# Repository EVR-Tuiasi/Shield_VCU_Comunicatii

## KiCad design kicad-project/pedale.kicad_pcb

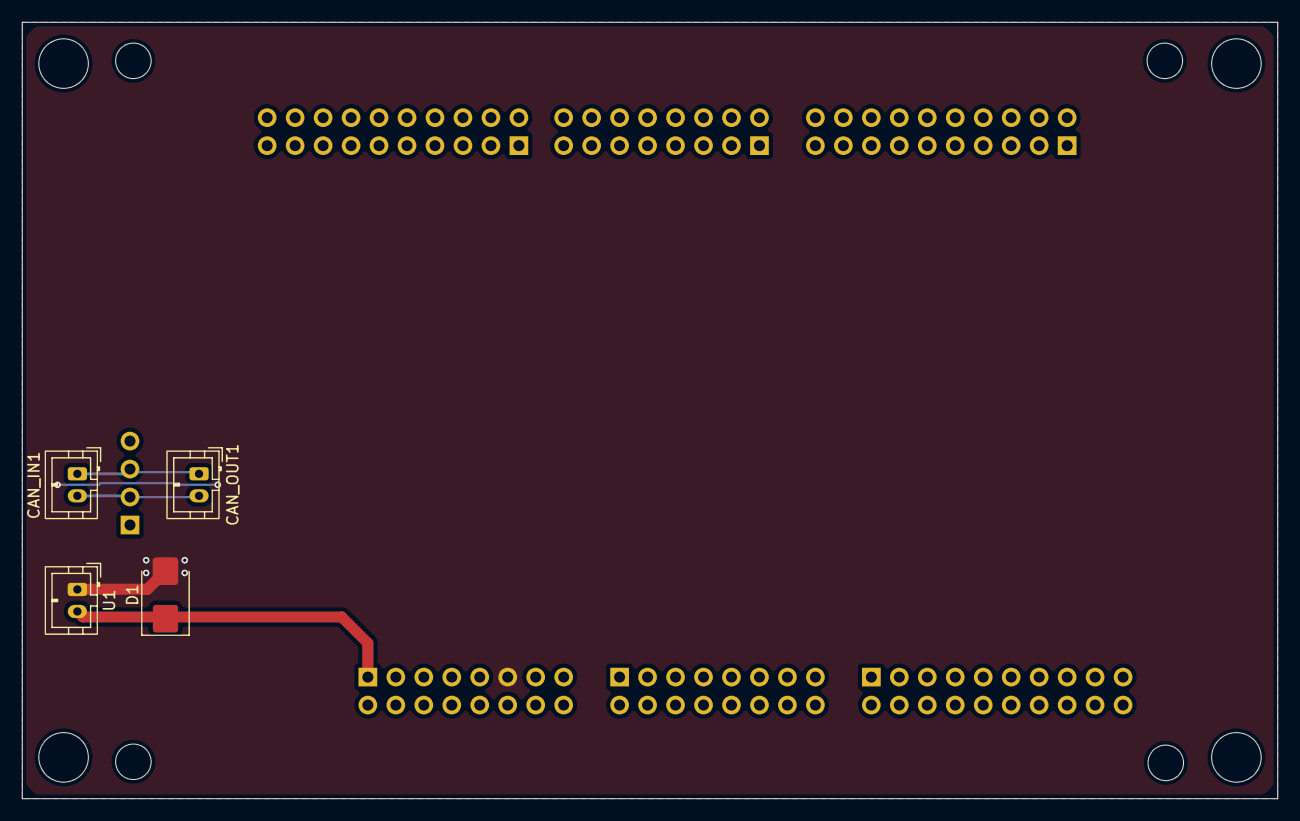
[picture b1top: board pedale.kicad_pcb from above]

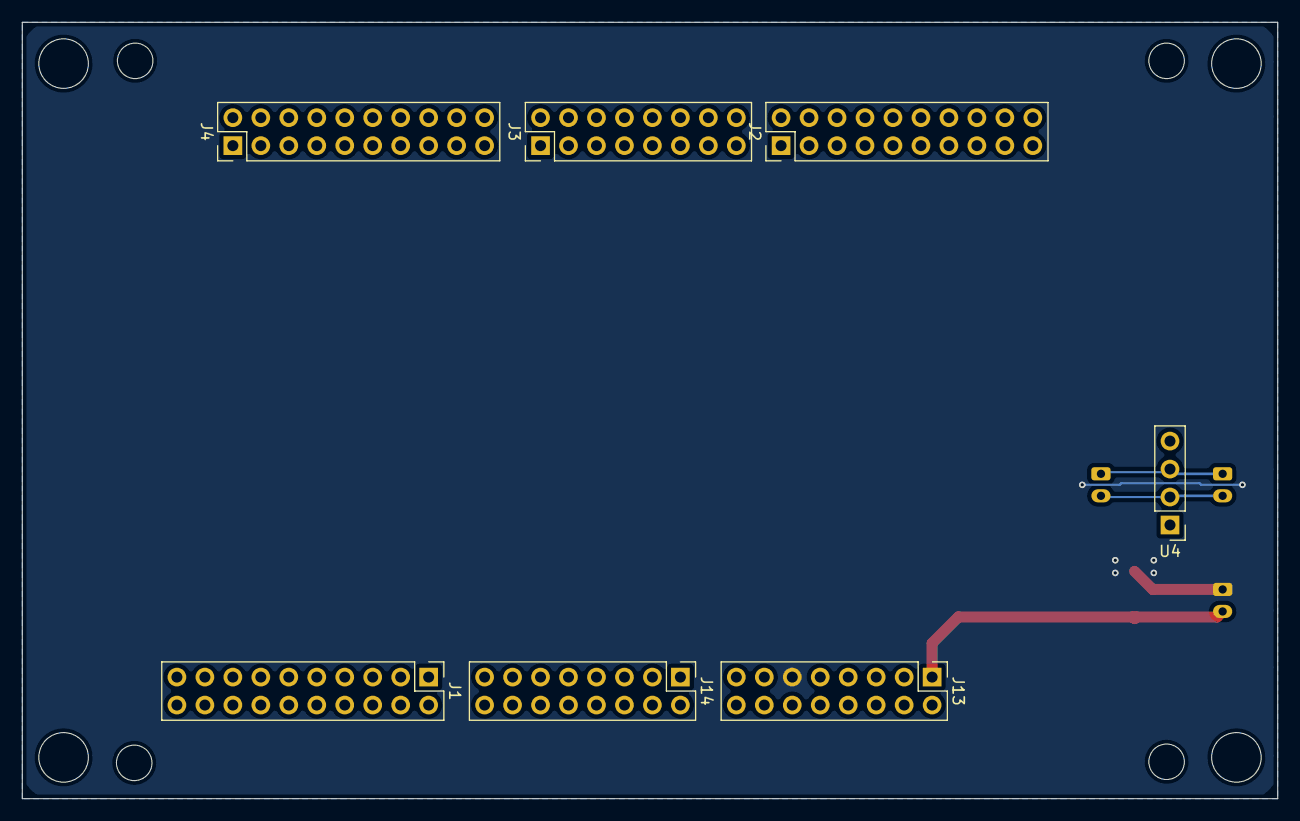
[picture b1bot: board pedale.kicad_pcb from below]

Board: 2 copper layers, 114.0 x 70.5 mm, 11 parts (7 on the bottom side), 4 nets.

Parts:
CAN_IN1: JST_PH_B2B-PH-K_1x02_P2.00mm_Vertical
CAN_OUT1: JST_PH_B2B-PH-K_1x02_P2.00mm_Vertical
D1: SS32; D_SMB
J1, J2, J4: PinHeader_2x10_P2.54mm_Vertical
J3, J13, J14: PinHeader_2x08_P2.54mm_Vertical
U1: JST_PH_B2B-PH-K_1x02_P2.00mm_Vertical
U4: PinHeader_1x04_P2.54mm_Vertical

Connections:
12V: D1.1 (K), J13.1 (VBAT), U1.2 (12V)
/CAN_N: CAN_IN1.2 (CANL), CAN_OUT1.2 (CANL), U4.2 (CANL)
/CAN_P: CAN_IN1.1 (CANH), CAN_OUT1.1 (CANH), U4.3 (CANH)
GND: D1.2 (A), J13.11 (GND), U1.1 (GND)

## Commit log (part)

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2026-03-22 upload proiect kicad
2026-03-23 modificari
2026-03-24 modificari dupa sugestii
2026-03-26 modificari 2
2026-03-26 viorel approved
2026-03-26 corectat footprint dioda
2026-05-06 step file
2026-06-15 CAN_IN & CAN_OUT - added
2026-06-25 Forgor
2026-06-29 GBR added + sent
